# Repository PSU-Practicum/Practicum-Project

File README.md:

Practicum-Project
=================

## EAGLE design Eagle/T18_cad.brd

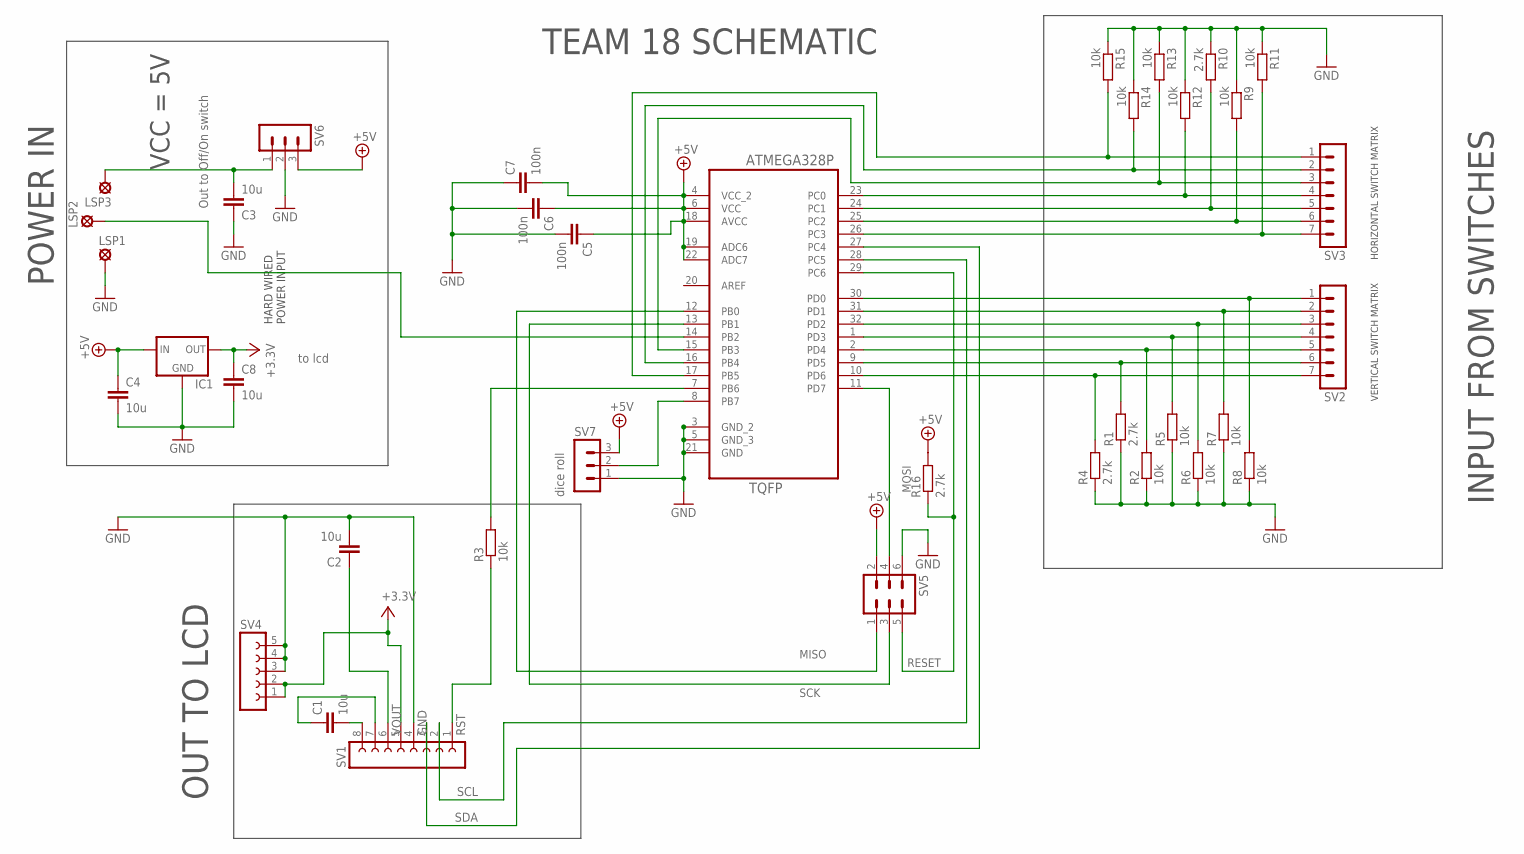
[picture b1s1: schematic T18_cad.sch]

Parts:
C1, C2, C3, C4, C8: 10u; C0603
C5, C6, C7: 100n; C0603
IC1: 78LXX
LSP1, LSP2, LSP3: SE14
R1, R4, R10, R16: 2.7k; R0603
R2, R3, R5, R6, R7, R8, R9, R11, R12, R13, R14, R15: 10k; R0603
SV1: FE08-1; FE08
SV2, SV3: MA07-1
SV4: FE05-1
SV5: MA03-2
SV6, SV7: MA03-1
U1: ATMEGA328P-AU; QFP80P900X900X120-32N

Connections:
+3.3V: C8.1, IC1.OUT, SV1.5, SV4.1, SV4.2
+5V: C4.1, C5.1, C6.1, C7.2, IC1.IN, R16.2, SV5.2, SV6.3, SV7.3, U1.4 (VCC_2), U1.6 (VCC), U1.18 (AVCC), U1.19 (ADC6), U1.22 (ADC7)
GND: C2.2, C3.1, C4.2, C5.2, C6.2, C7.1, C8.2, IC1.GND, LSP1.MP, R1.1, R2.1, R4.1, R5.1, R6.1, R7.1, R8.1, R9.1, R10.1, R11.1, R12.1, R13.1, R14.1, R15.1, SV1.4, SV4.3, SV4.4, SV4.5, SV5.6, SV6.2, SV7.1, U1.3 (GND_2), U1.5 (GND_3), U1.21 (GND)
MISO: SV5.1, U1.12 (PB0)
MOSI: SV5.4, U1.11 (PD7)
unnamed: R1.2, SV2.6, U1.9 (PD5)
unnamed: LSP2.MP, U1.14 (PB2)
unnamed: R5.2, SV2.4, U1.1 (PD3)
unnamed: R2.2, SV2.5, U1.2 (PD4)
unnamed: R6.2, SV2.3, U1.32 (PD2)
unnamed: R7.2, SV2.2, U1.31 (PD1)
unnamed: R8.2, SV2.1, U1.30 (PD0)
unnamed: R4.2, SV2.7, U1.10 (PD6)
unnamed: R11.2, SV3.7, U1.26 (PC3)
unnamed: C1.2, SV1.8
unnamed: C3.2, LSP3.MP, SV6.1
unnamed: R3.2, U1.7 (PB6)
unnamed: C1.1, SV1.7
unnamed: R9.2, SV3.6, U1.25 (PC2)
unnamed: R10.2, SV3.5, U1.24 (PC1)
unnamed: R12.2, SV3.4, U1.23 (PC0)
unnamed: R13.2, SV3.3, U1.15 (PB3)
unnamed: R14.2, SV3.2, U1.16 (PB4)
unnamed: R15.2, SV3.1, U1.17 (PB5)
RESET: R16.1, SV5.5, U1.29 (PC6)
RST: R3.1, SV1.1
SCK: SV5.3, U1.13 (PB1)
SCL: SV1.2, U1.28 (PC5)
SDA: SV1.3, U1.27 (PC4)
TESTPT: SV7.2, U1.8 (PB7)
VOUT: C2.1, SV1.6

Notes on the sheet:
TEAM 18 SCHEMATIC
OUT TO LCD
VERTICAL SWITCH MATRIX
HORIZONTAL SWITCH MATRIX
HARD WIRED POWER INPUT
VCC = 5V
INPUT FROM SWITCHES
POWER IN
Out to Off/On switch
dice roll
to lcd

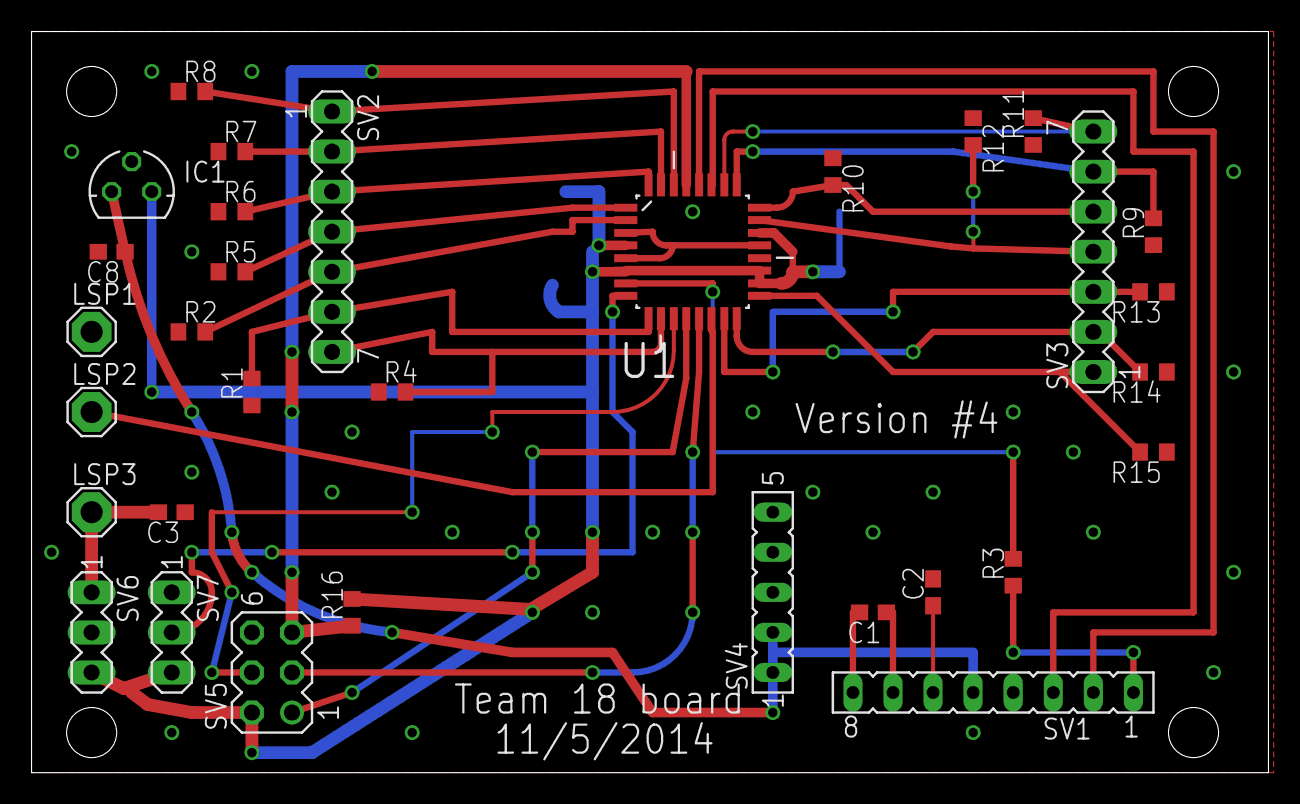
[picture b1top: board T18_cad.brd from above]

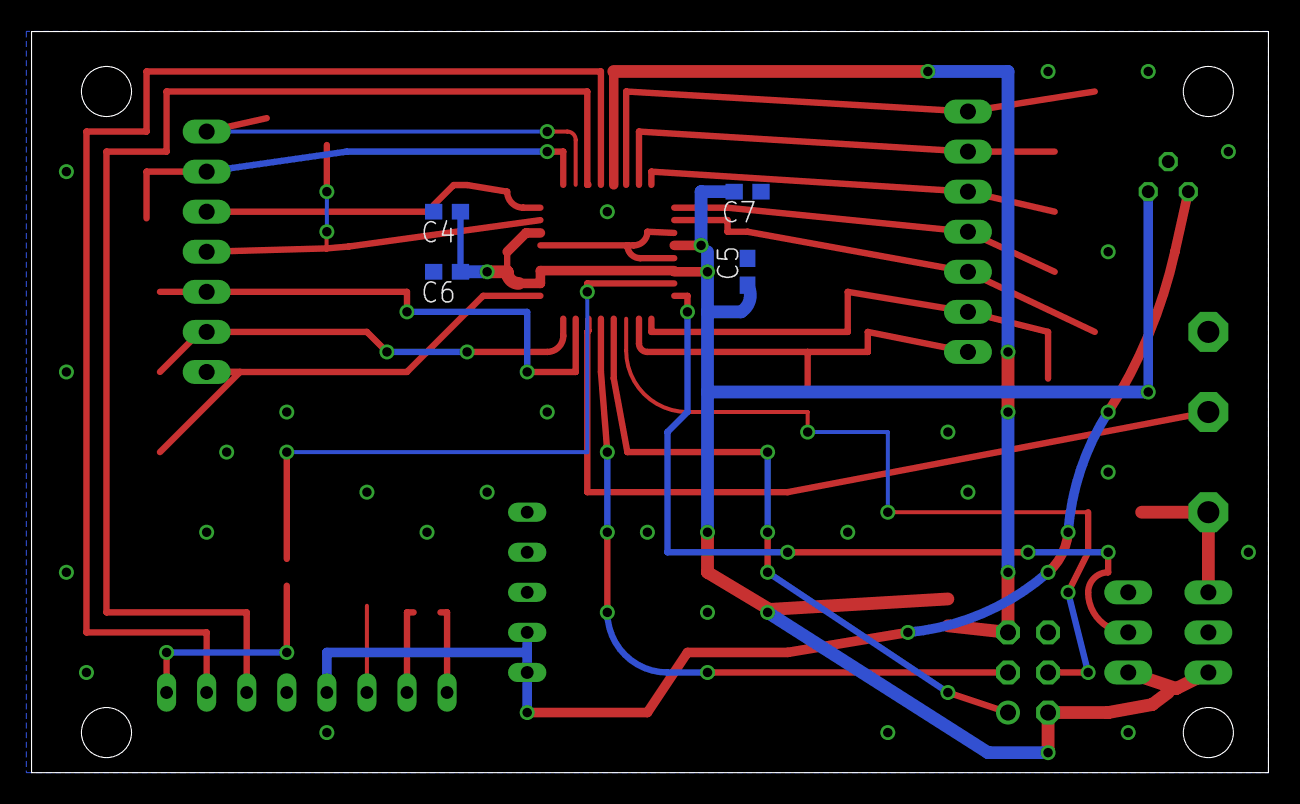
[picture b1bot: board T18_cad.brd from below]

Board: 2 copper layers, 78.4 x 47.0 mm, 36 parts (4 on the bottom side), 31 nets.

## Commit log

2014-10-11 project description
2014-10-23 Added folders, added files under misc.
2014-11-04 Revert "Initial commit"
    This reverts commit eca54e84fef6ad286aea21a95ff66c0d246ce4ea.
2014-11-10 Showing Daniel whats up
2014-11-10 Added a dummy text
    Just testing out the upload
2014-11-10 Removed the dummy text
    test complete, removing unneeded file
2014-11-10 clean up some files
    changed name of c code, got rid of unnecessary files.
2014-11-10 text to word files
    Changed past assignments from text files to word files so they would
    show properly when linked to.
2014-11-12 Enclosure Design Update
    Started adding the enclosure design files.
2014-11-14 Enclosure Design Summary
    Finished Design, removed temp files
2014-11-15 Create Bill of Materials
2014-11-18 Project Model homework
2014-11-18 Rename Folder
2014-11-19 Create TWI initialization
2014-11-19 Update TWI initialization
2014-11-20 Update Enclosure Design
    Added file for the bottom of enclosure (with fingering!) and file for
    pieces of optical isolation grid.
2014-11-26 Finished LED grid and OI grid
    If you want to cut these pieces, let me know first. We don't need any
    duplicates.
2014-11-26 Isolation grid not ready.
    I put the wrong file in here, the new one is possibly on my USB drive.
    Will update.
2014-11-27 Updated enclosure design
    Uploaded new design file.
2014-12-02 Did more things!
2014-12-02 Enclosure vector graphics
2014-12-03 Test plan and test cases for tablero game board
2014-12-12 Final Update
    BOM, Final code, some other organizational stuff
